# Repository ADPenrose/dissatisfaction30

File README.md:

# Dissatisfaction30 Macropad

This branch is a modification of the original project. ISO layout, underglow and an extra encoder are supported in this version.

[Keyboard Layout Editor (KLE)](http://www.keyboard-layout-editor.com/##@_name=Dissatisfaction%2030&author=dcpedit,%20adpenrose%3B&@=Esc%0A%0A%0A%0A%0A%0A%0A%0A%0Ae0&_x:0.25%3B&=F1&=F2&=F3&_x:0.25%3B&=F4&=F5&=F6&_x:1.5%3B&=Mute%0A%0A%0A%0A%0A%0A%0A%0A%0Ae1%3B&@_y:-0.75&x:7.75&c=%238c8c8c&a:7&h:2%3B&=OLED%3B&@_c=%23cccccc&a:4%3B&=Tab&=Q&=W&=E&=R&=T&_c=%23cc7070&w:1.5%3B&=Backspace&_x:1.5&c=%23cccccc%3B&=Insert&_x:1.75&c=%23cc7070&w:1.25&h:2&w2:1.5&h2:1&x2:-0.25%3B&=Enter%3B&@_c=%23cccccc&w:1.25%3B&=Shift&=A&=S&=D&=F&_c=%23cc7070&w:2.25%3B&=Enter&_x:1.5&c=%23cccccc%3B&=Delete&_x:0.75&c=%23cc7070%3B&=G%3B&@_y:-0.75&x:7.75&c=%23cccccc%3B&=↑%3B&@_y:-0.25%3B&=Ctrl&_w:1.25%3B&=Alt&_a:7&w:2%3B&=&_a:4&w:1.25%3B&=Alt&=Ctrl%3B&@_y:-0.75&x:6.75%3B&=←&=↓&=→)

# Image Gallery
https://imgur.com/a/5sZTefW

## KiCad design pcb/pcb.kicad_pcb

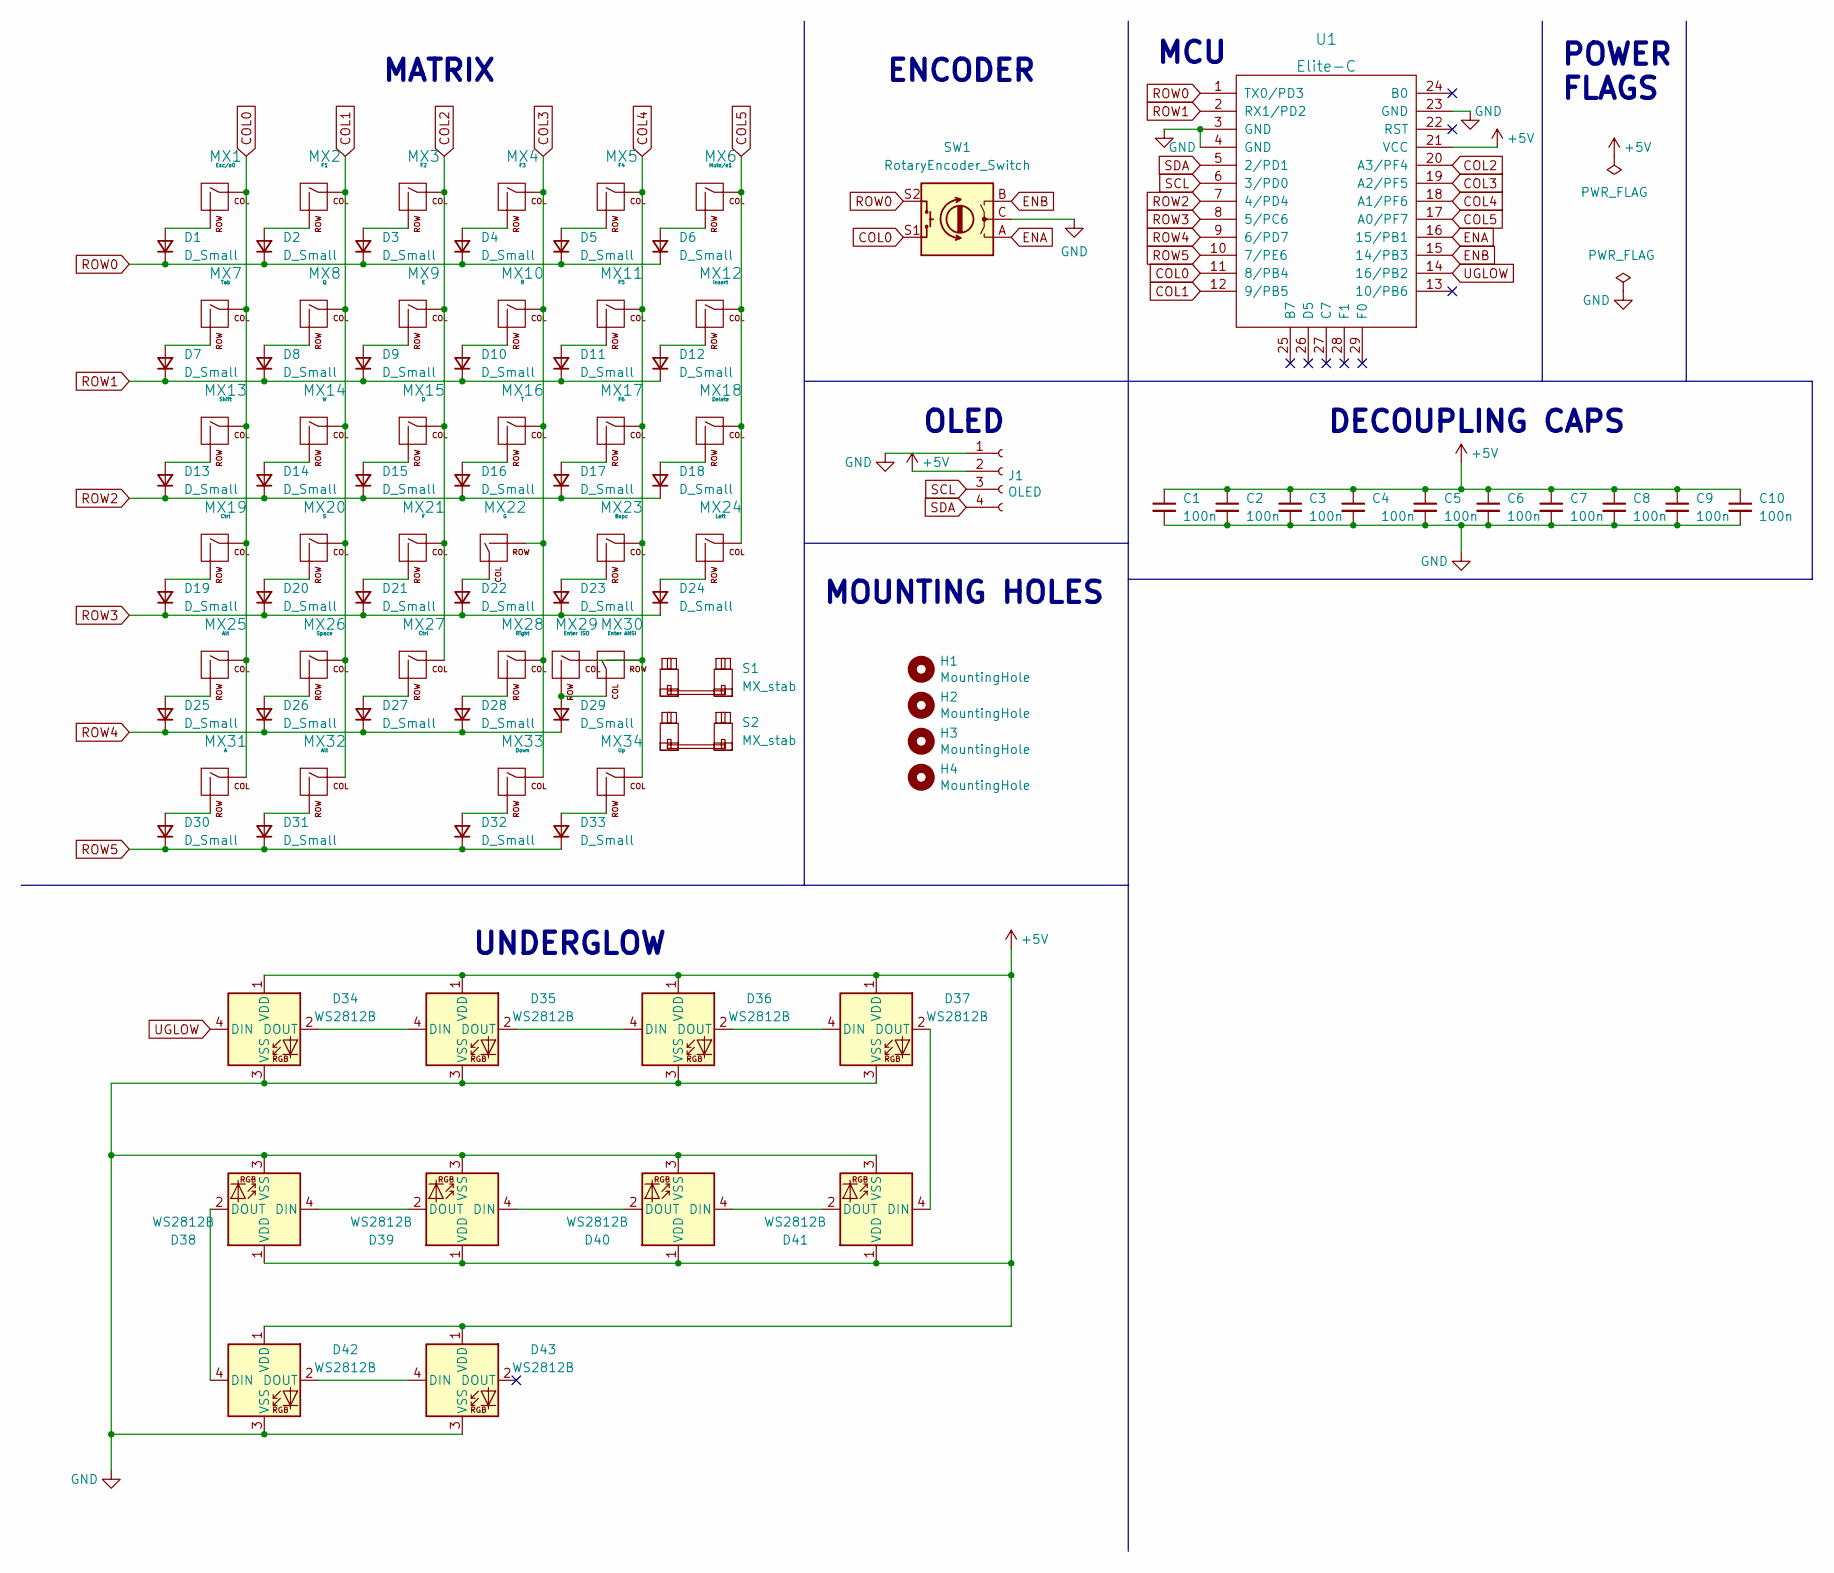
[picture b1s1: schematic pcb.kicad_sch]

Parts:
C1, C2, C3, C4, C5, C6, C7, C8, C9, C10: 100n; C_0805_2012Metric_Pad1.18x1.45mm_HandSolder
D1, D2, D3, D4, D5, D6, D7, D8, D9, D10, D11, D12, D13, D14, D15, D16, D17, D18, D19, D20, D21, D22, D23, D24, D25, D26, D27, D28, D29, D30, D31, D32, D33: D_Small; Diode-dual-onesided
D34, D35, D36, D37, D38, D39, D40, D41, D42, D43: WS2812B; LED_WS2812B_PLCC4_5.0x5.0mm_P3.2mm
H1, H2, H3, H4: MountingHole; MountingHole_2.2mm_M2_Pad
J1: OLED; SSD1306_OLED
MX1: Esc/e0; MX100H
MX2: F1; MX100H
MX3: F2; MX100H
MX4: F3; MX100H
MX5: F4; MX100H
MX6: Mute/e1; MX100H
MX7: Tab; MX100H
MX8: Q; MX100H
MX9: E; MX100H
MX10: R; MX100H
MX11: F5; MX100H
MX12: Insert; MX100H
MX13: Shift; MX125H
MX14: W; MX100H
MX15: D; MX100H
MX16: T; MX100H
MX17: F6; MX100H
MX18: Delete; MX100H
MX19, MX27: Ctrl; MX100H
MX20: S; MX100H
MX21: F; MX100H
MX22: G; MX100H
MX23: Bspc; MX100H
MX24: Left; MX100H
MX25, MX32: Alt; MX125H
MX26: Space; MX200H
MX28: Right; MX100H
MX29: Enter ISO; MX100H
MX30: Enter ANSI; MX100H
MX31: A; MX100H
MX33: Down; MX100H
MX34: Up; MX100H
S1: MX_stab; STAB_MX_2.25u
S2: MX_stab; STAB_MX_ISO_FLIPPED
SW1: RotaryEncoder_Switch; RotaryEncoder_EC11-no-legs
U1: Elite-C; Elite-C-castellated-29pin-holes

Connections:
+5V: C1.1, C2.1, C3.1, C4.1, C5.1, C6.1, C7.1, C8.1, C9.1, C10.1, D34.1 (VDD), D35.1 (VDD), D36.1 (VDD), D37.1 (VDD), D38.1 (VDD), D39.1 (VDD), D40.1 (VDD), D41.1 (VDD), D42.1 (VDD), D43.1 (VDD), J1.2, U1.21 (VCC)
COL0: MX1.1 (COL), MX7.1 (COL), MX13.1 (COL), MX19.1 (COL), MX25.1 (COL), MX31.1 (COL), SW1.S1, U1.11 (8/PB4)
COL1: MX2.1 (COL), MX8.1 (COL), MX14.1 (COL), MX20.1 (COL), MX26.1 (COL), MX32.1 (COL), U1.12 (9/PB5)
COL2: MX3.1 (COL), MX9.1 (COL), MX15.1 (COL), MX21.1 (COL), MX27.1 (COL), U1.20 (A3/PF4)
COL3: MX4.1 (COL), MX10.1 (COL), MX16.1 (COL), MX22.2 (ROW), MX28.1 (COL), MX33.1 (COL), U1.19 (A2/PF5)
COL4: MX5.1 (COL), MX11.1 (COL), MX17.1 (COL), MX23.1 (COL), MX29.1 (COL), MX30.2 (ROW), MX34.1 (COL), U1.18 (A1/PF6)
COL5: MX6.1 (COL), MX12.1 (COL), MX18.1 (COL), MX24.1 (COL), U1.17 (A0/PF7)
ENA: SW1.A, U1.16 (15/PB1)
ENB: SW1.B, U1.15 (14/PB3)
GND: C1.2, C2.2, C3.2, C4.2, C5.2, C6.2, C7.2, C8.2, C9.2, C10.2, D34.3 (VSS), D35.3 (VSS), D36.3 (VSS), D37.3 (VSS), D38.3 (VSS), D39.3 (VSS), D40.3 (VSS), D41.3 (VSS), D42.3 (VSS), D43.3 (VSS), J1.1, SW1.C, U1.3 (GND), U1.4 (GND), U1.23 (GND)
unnamed: D1.2 (A), MX1.2 (ROW)
unnamed: D2.2 (A), MX2.2 (ROW)
unnamed: D3.2 (A), MX3.2 (ROW)
unnamed: D4.2 (A), MX4.2 (ROW)
unnamed: D5.2 (A), MX5.2 (ROW)
unnamed: D6.2 (A), MX6.2 (ROW)
unnamed: D7.2 (A), MX7.2 (ROW)
unnamed: D8.2 (A), MX8.2 (ROW)
unnamed: D9.2 (A), MX9.2 (ROW)
unnamed: D10.2 (A), MX10.2 (ROW)
unnamed: D11.2 (A), MX11.2 (ROW)
unnamed: D12.2 (A), MX12.2 (ROW)
unnamed: D13.2 (A), MX13.2 (ROW)
unnamed: D14.2 (A), MX14.2 (ROW)
unnamed: D15.2 (A), MX15.2 (ROW)
unnamed: D16.2 (A), MX16.2 (ROW)
unnamed: D17.2 (A), MX17.2 (ROW)
unnamed: D18.2 (A), MX18.2 (ROW)
unnamed: D19.2 (A), MX19.2 (ROW)
unnamed: D20.2 (A), MX20.2 (ROW)
unnamed: D21.2 (A), MX21.2 (ROW)
unnamed: D22.2 (A), MX22.1 (COL)
unnamed: D23.2 (A), MX23.2 (ROW)
unnamed: D24.2 (A), MX24.2 (ROW)
unnamed: D25.2 (A), MX25.2 (ROW)
unnamed: D26.2 (A), MX26.2 (ROW)
unnamed: D27.2 (A), MX27.2 (ROW)
unnamed: D28.2 (A), MX28.2 (ROW)
unnamed: D29.2 (A), MX29.2 (ROW), MX30.1 (COL)
unnamed: D30.2 (A), MX31.2 (ROW)
unnamed: D31.2 (A), MX32.2 (ROW)
unnamed: D32.2 (A), MX33.2 (ROW)
unnamed: D33.2 (A), MX34.2 (ROW)
unnamed: D34.2 (DOUT), D35.4 (DIN)
unnamed: D35.2 (DOUT), D36.4 (DIN)
unnamed: D36.2 (DOUT), D37.4 (DIN)
unnamed: D38.2 (DOUT), D42.4 (DIN)
unnamed: D38.4 (DIN), D39.2 (DOUT)
unnamed: D39.4 (DIN), D40.2 (DOUT)
unnamed: D40.4 (DIN), D41.2 (DOUT)
unnamed: D37.2 (DOUT), D41.4 (DIN)
unnamed: D42.2 (DOUT), D43.4 (DIN)
ROW0: D1.1 (K), D2.1 (K), D3.1 (K), D4.1 (K), D5.1 (K), D6.1 (K), SW1.S2, U1.1 (TX0/PD3)
ROW1: D7.1 (K), D8.1 (K), D9.1 (K), D10.1 (K), D11.1 (K), D12.1 (K), U1.2 (RX1/PD2)
ROW2: D13.1 (K), D14.1 (K), D15.1 (K), D16.1 (K), D17.1 (K), D18.1 (K), U1.7 (4/PD4)
ROW3: D19.1 (K), D20.1 (K), D21.1 (K), D22.1 (K), D23.1 (K), D24.1 (K), U1.8 (5/PC6)
ROW4: D25.1 (K), D26.1 (K), D27.1 (K), D28.1 (K), D29.1 (K), U1.9 (6/PD7)
ROW5: D30.1 (K), D31.1 (K), D32.1 (K), D33.1 (K), U1.10 (7/PE6)
SCL: J1.3, U1.6 (3/PD0)
SDA: J1.4, U1.5 (2/PD1)
UGLOW: D34.4 (DIN), U1.14 (16/PB2)

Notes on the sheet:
DECOUPLING CAPS
MOUNTING HOLES
POWER FLAGS
OLED
MATRIX
UNDERGLOW
MCU
ENCODER

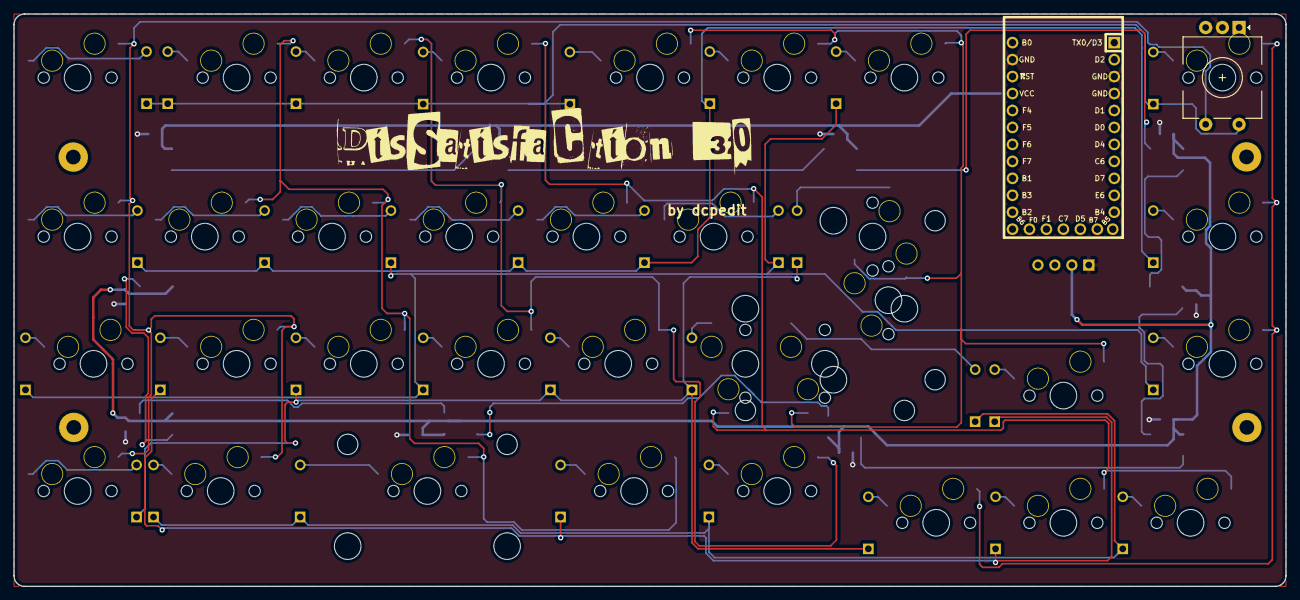
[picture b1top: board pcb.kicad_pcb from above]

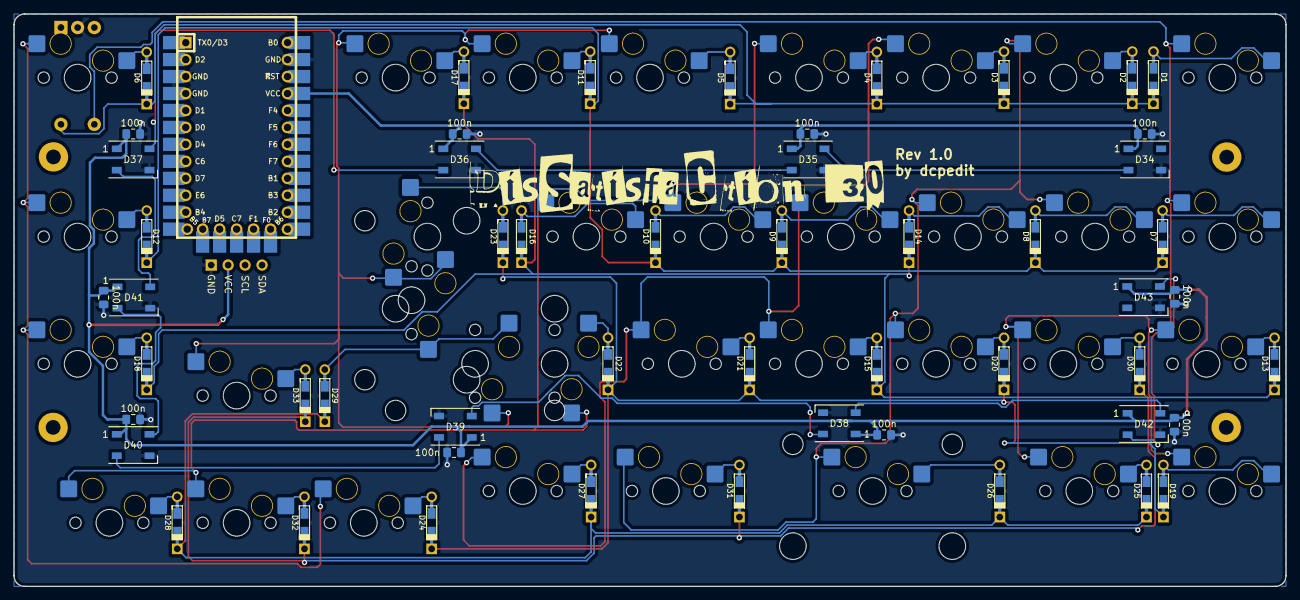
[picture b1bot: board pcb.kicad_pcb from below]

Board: 2 copper layers, 190.5 x 85.7 mm, 96 parts (88 on the bottom side), 61 nets.

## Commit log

2023-01-07 Modified README.md file.
2023-01-07 Added initial modifications to the schematic.
2023-01-07 Added initial modified files.
2023-01-09 Added keyboard matrix references.
2023-01-11 Finished tentative schematic and imported footprints into the PCB file.
2023-01-14 Modified Elite-C footprint.
2023-01-14 Added footprints for most of the parts to the PCB file.
2023-01-15 Added missing LEDs and caps.
2023-01-18 Routed power and switch matrix. Pending connections to the MCU.
2023-01-21 Routed LEDs.
2023-01-25 Finished routing.
